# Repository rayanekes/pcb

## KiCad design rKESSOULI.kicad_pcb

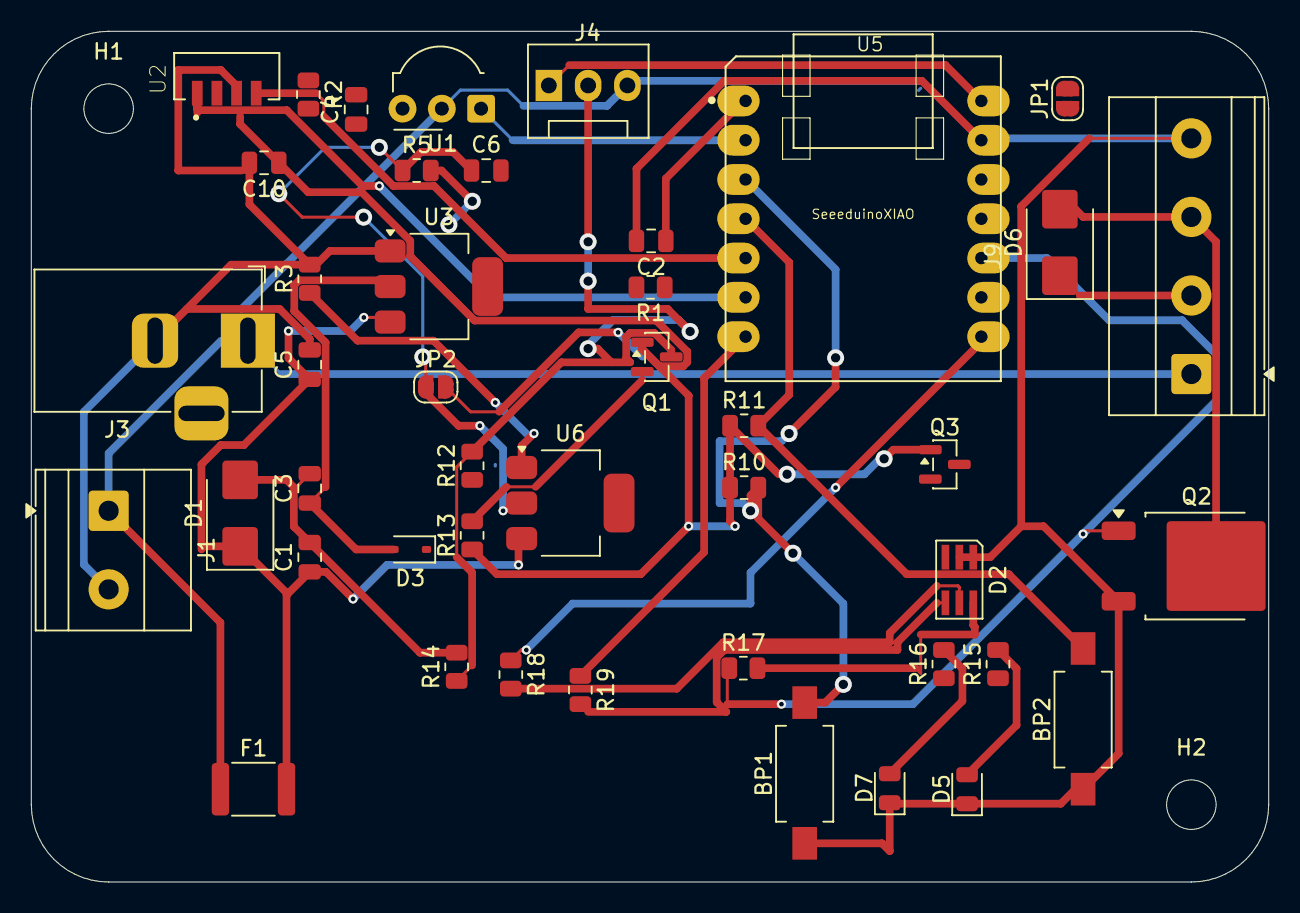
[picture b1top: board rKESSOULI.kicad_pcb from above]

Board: 2 copper layers, 80.0 x 55.0 mm, 46 parts (0 on the bottom side), 29 nets.

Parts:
BP1, BP2: SW_Push; FSMSM_PushButton
C1, C2, C3, C4, C5, C6, C10: C; C_0805_2012Metric
D1, D6: D; D_SMB
D2: LED_RGB; LED_Avago_PLCC6_3x2.8mm
D3: D_Schottky; D_SOD-323
D5, D7: LED; LED_0805_2012Metric
F1: Polyfuse; Fuse_1812_4532Metric
H1, H2: MountingHole; MountingHole_3.2mm_M3_ISO14580
J1: Conn_01x02_Socket; TerminalBlock_Phoenix_MKDS-1,5-2-5.08_1x02_P5.08mm_Horizont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
J3: Barrel_Jack_MountingPin; BarrelJack_Horizontal
J4: Conn_01x03_Pin; FanPinHeader_1x03_P2.54mm_Vertical
J9: Conn_01x04_Socket; TerminalBlock_Phoenix_MKDS-1,5-4-5.08_1x04_P5.08mm_Horizont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
JP1: SolderJumper_2_Open; SolderJumper-2_P1.3mm_Open_RoundedPad1.0x1.5mm
JP2: SolderJumper_3_Open; SolderJumper-2_P1.3mm_Open_RoundedPad1.0x1.5mm
Q1: Q_NMOS_GSD; SOT-23
Q2: Q_NMOS_GDS; TO-252-2
Q3: SFH3711; SOT-23
R1, R2, R3, R5, R10, R11, R12, R13, R14, R15, R16, R17, R18, R19: R; R_0805_2012Metric
U1: TSOP4838; Vishay_MOLD-3Pin
U2: VEML7700; XDCR_VEML7700-TT
U3: NCP1117-1.5_SOT223; SOT-223-3_TabPin2
U5: SeeeduinoXIAO; Seeeduino XIAO-MOUDLE14P-barettes
U6: LM317_SOT-223; SOT-223-3_TabPin2

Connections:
+3.3V: C10.1, Q1.1 (G), Q3.1 (C), R2.2, R10.1, R11.1, R13.1, U2.2 (VDD), U5.12 (3V3)
+5V: D3.1 (K), J4.1, R12.1, U5.14 (5V)
/BP1: BP1.2, R10.2, U5.3 (PA10_A2_D2)
/BP2: BP2.2, R11.2, U5.4 (PA11_A3_D3)
/DCIN: F1.1, J1.1, J3.1, J9.1
/DCIN_F: C1.1, C5.1, D1.1 (K), F1.2, U3.3 (VI), U6.3 (VI)
/IR: U1.1 (OUT), U5.2 (PA4_A1_D1)
/LED1: Q1.2 (S), R13.2, R15.1, U5.11 (PA6_A10_D10_MOSI)
/LED2: R16.1, U5.9 (PA7_A8_D8_SCK)
/LIGHT1: C2.1, Q3.2 (E), R1.1, U5.1 (PA02_A0_D0)
/RGB_B/PWM: Q2.1 (G), R17.1, U5.10 (PA5_A9_D9_MISO)
/RGB_G: R18.1, U5.8 (PB09_A7_D7_RX)
/RGB_R: R19.1, U5.7 (PB08_A6_D6_TX)
/SCL_3V: U2.1 (SCL), U5.6 (PA9_A5_D5_SCL)
/SDA_3V: U2.4 (SDA), U5.5 (PA8_A4_D4_SDA)
/V_LAMPE: JP1.1 (A), JP2.2 (C)
GND: BP1.1, BP2.1, C1.2, C2.2, C3.2, C4.2, C5.2, C6.2, C10.2, D1.2 (A), D2.1 (RK), D2.2 (GK), D2.3 (BK), D5.1 (K), D7.1 (K), J1.2, J3.2, J4.3, J9.4, Q2.3 (S), R1.2, R3.2, R14.2, U1.2 (GND), U2.3 (GND), U3.1 (GND), U5.13 (GND)
unnamed: D2.4 (BA), R19.2
unnamed: D2.5 (GA), R18.2
unnamed: D2.6 (RA), R17.2
unnamed: C3.1, D3.2 (A), U3.2 (VO)
unnamed: D5.2 (A), R15.2
unnamed: D6.2 (A), J9.3, Q2.2 (D)
unnamed: D6.1 (K), J9.2, JP1.2 (B)
unnamed: D7.2 (A), R16.2
unnamed: J4.2, Q1.3 (D), R12.2, R14.1
unnamed: C6.1, JP2.1 (A), R5.1, U6.2 (VO)
unnamed: C4.1, R2.1, U1.3 (Vs)
unnamed: R3.1, R5.2, U6.1 (ADJ)
